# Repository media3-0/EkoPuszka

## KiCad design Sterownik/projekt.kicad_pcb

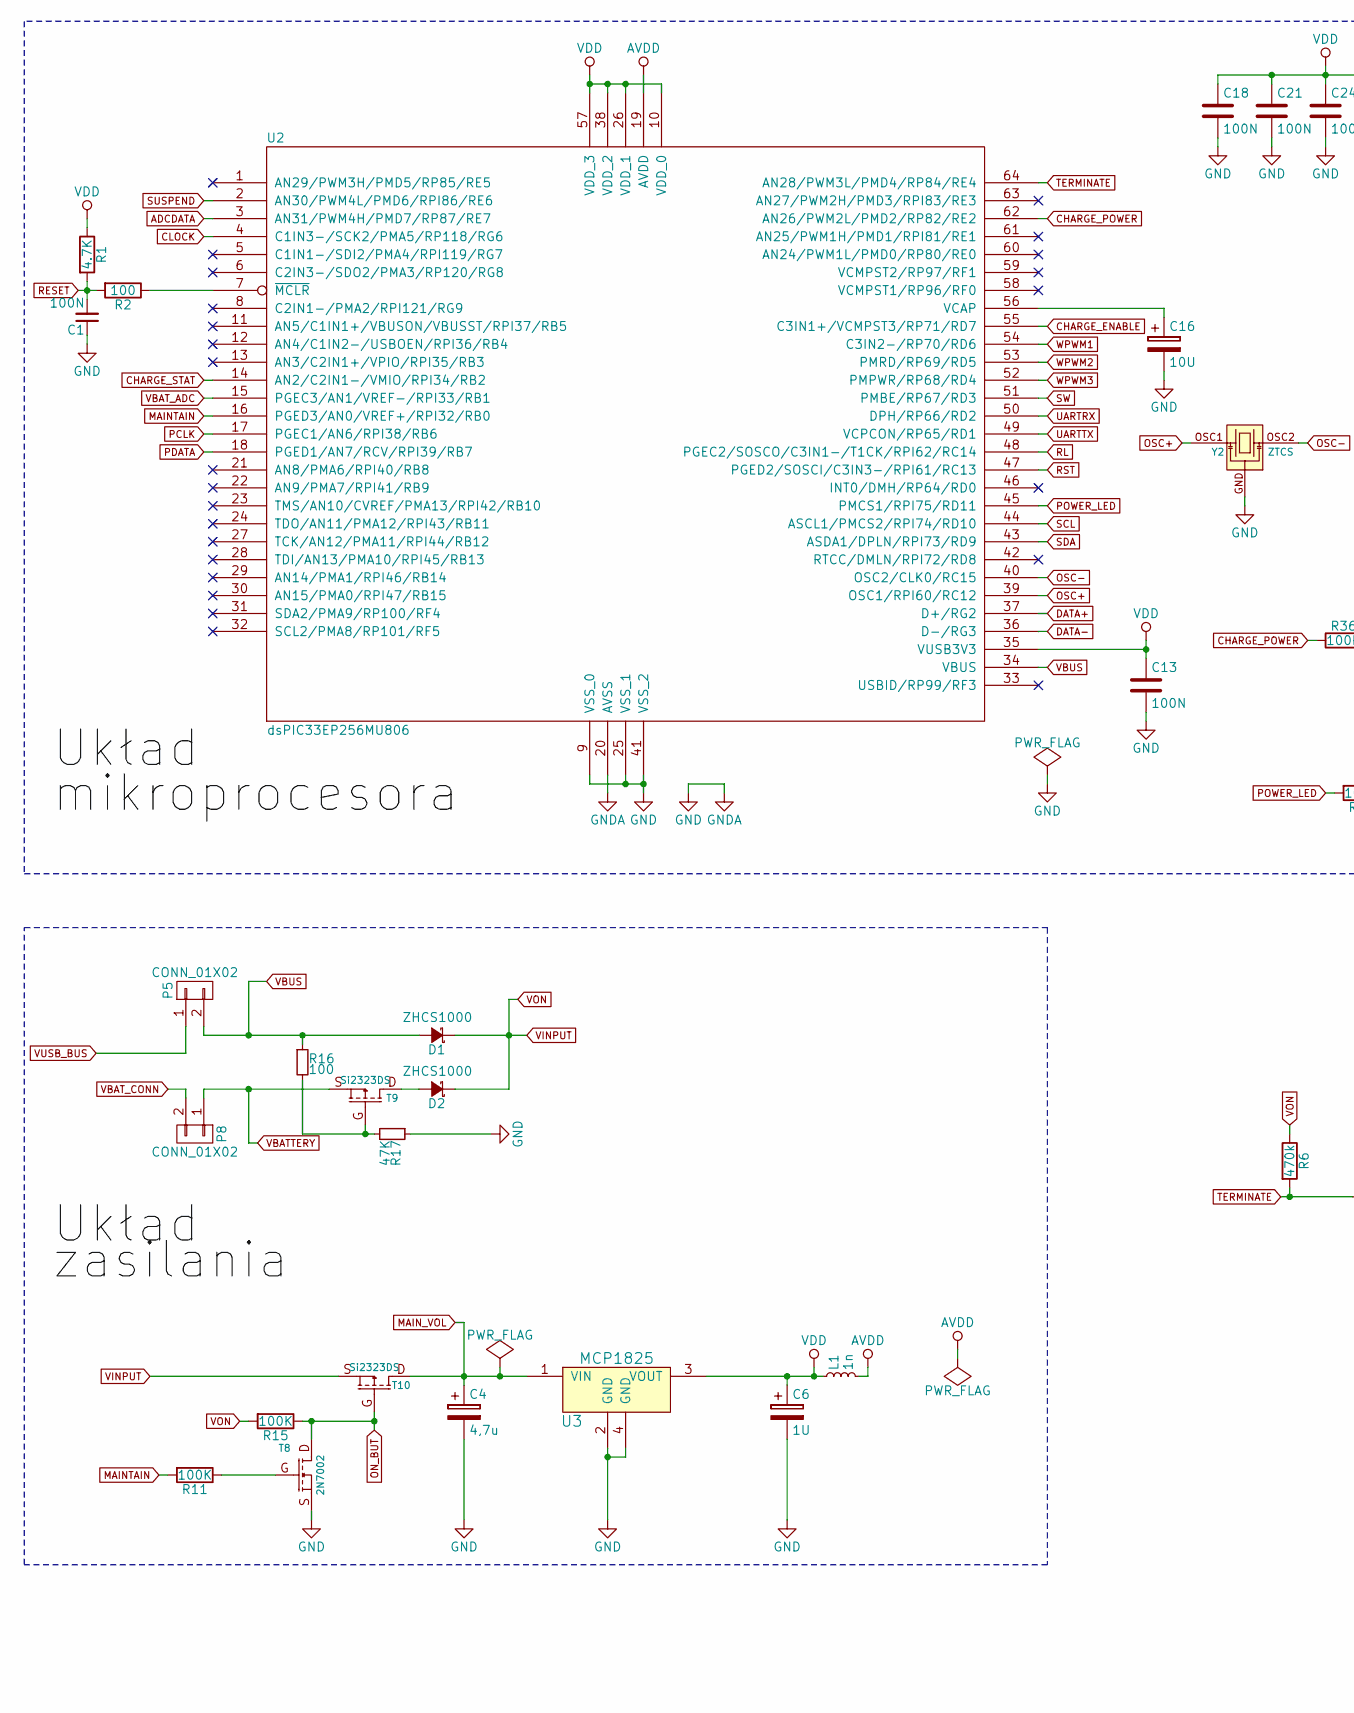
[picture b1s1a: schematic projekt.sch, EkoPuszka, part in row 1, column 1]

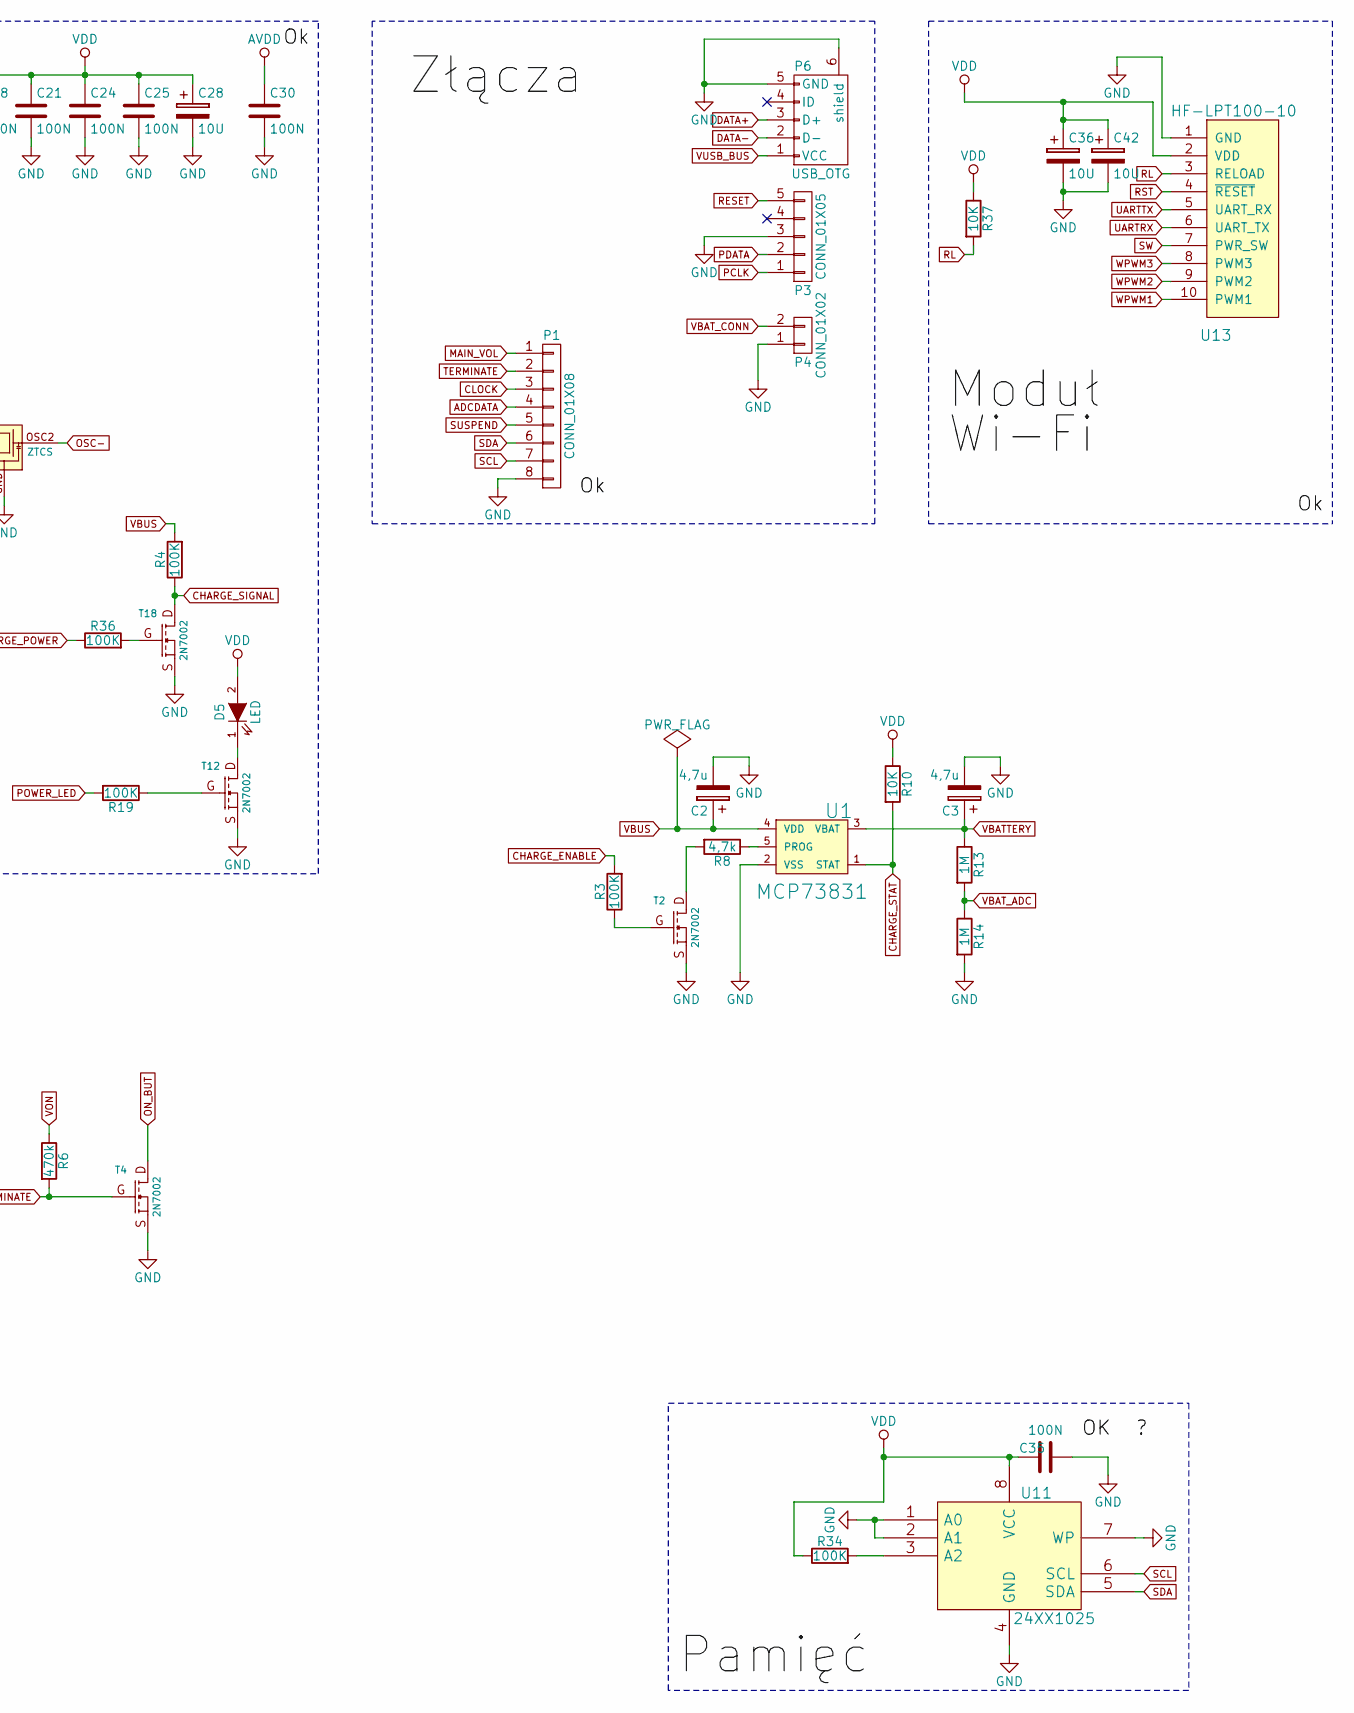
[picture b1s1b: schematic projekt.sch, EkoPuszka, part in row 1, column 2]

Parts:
C1, C13, C18, C21, C24, C25, C30, C35: 100N; C_0603_HandSoldering
C2, C3, C4: 4,7u; TantalC_SizeA_EIA-3216_HandSoldering
C6: 1U; C_2220_HandSoldering
C16: 10U; TantalC_SizeX_EIA-7343
C28, C36, C42: 10U; SMD-1206_Pol
D1, D2: ZHCS1000; SOT23-ZHCS1000
D5: LED; LED-1206
L1: 1n; R_0603
P1: CONN_01X08; DS1065-02-1X8S8BS
P3: CONN_01X05; Socket_Strip_Straight_1x05
P4: CONN_01X02; Socket_Strip_Straight_1x02
P5, P8: CONN_01X02; Pin_Header_Straight_1x02
P6: USB_OTG; USB_Mini-B
R1: 4.7K; R_0603
R2, R16: 100; R_0603
R3, R4, R11, R15, R19, R34, R36: 100K; R_0603
R6: 470k; R_0603
R8: 4,7k; R_0603
R10, R37: 10K; R_0603
R13, R14: 1M; R_0603
R17: 47K; R_0603
T2, T4, T8, T12, T18: 2N7002; 2N7002-SOT23
T9, T10: Si2323DS; SOT23
U1: MCP73831; SOT-23-5
U2: dsPIC33EP256MU806; TQFP-64_10x10mm_Pitch0.5mm
U3: MCP1825; SOT-223
U11: 24XX1025; SOIC-8-N
U13: HF-LPT100-10
Y2: ZTCS; ZTTCS

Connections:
ADCDATA: P1.4, U2.3 (AN31/PWM4H/PMD7/RP87/RE7)
AVDD: C30.1, L1.2, U2.19 (AVDD)
CHARGE_ENABLE: R3.2, U2.55 (C3IN1+/VCMPST3/RP71/RD7)
CHARGE_POWER: R36.1, U2.62 (AN26/PWM2L/PMD2/RP82/RE2)
CHARGE_SIGNAL: R4.1, T18.D
CHARGE_STAT: R10.2, U1.1 (STAT), U2.14 (AN2/C2IN1-/VMIO/RPI34/RB2)
CLOCK: P1.3, U2.4 (C1IN3-/SCK2/PMA5/RP118/RG6)
DATA+: P6.3 (D+), U2.37 (D+/RG2)
DATA-: P6.2 (D-), U2.36 (D-/RG3)
GND: C1.1, C2.2, C3.2, C4.2, C6.2, C13.2, C16.2, C18.2, C21.2, C24.2, C25.2, C28.2, C30.2, C35.1, C36.2, C42.2, P1.8, P3.3, P4.1, P6.5 (GND), P6.6 (shield), R14.2, R17.1, T2.S, T4.S, T8.S, T12.S, T18.S, U1.2 (VSS), U2.9 (VSS_0), U2.20 (AVSS), U2.25 (VSS_1), U2.41 (VSS_2), U3.2 (GND), U3.4 (GND), U11.1 (A0), U11.2 (A1), U11.4 (GND), U11.7 (WP), U13.1 (GND), Y2.GND
MAINTAIN: R11.2, U2.16 (PGED3/AN0/VREF+/RPI32/RB0)
MAIN_VOL: C4.1, P1.1, T10.D, U3.1 (VIN)
unnamed: C16.1, U2.56 (VCAP)
unnamed: D2.A, T9.D
unnamed: D5.1 (K), T12.D
unnamed: R2.1, U2.7 (~MCLR~)
unnamed: R3.1, T2.G
unnamed: R8.1, U1.5 (PROG)
unnamed: R8.2, T2.D
unnamed: R11.1, T8.G
unnamed: R16.2, R17.2, T9.G
unnamed: R19.1, T12.G
unnamed: R34.2, U11.3 (A2)
unnamed: R36.2, T18.G
ON_BUT: R15.1, T4.D, T8.D, T10.G
OSC+: U2.39 (OSC1/RPI60/RC12), Y2.OSC1
OSC-: U2.40 (OSC2/CLK0/RC15), Y2.OSC2
PCLK: P3.1, U2.17 (PGEC1/AN6/RPI38/RB6)
PDATA: P3.2, U2.18 (PGED1/AN7/RCV/RPI39/RB7)
POWER_LED: R19.2, U2.45 (PMCS1/RPI75/RD11)
RESET: C1.2, P3.5, R1.2, R2.2
RL: R37.2, U2.48 (PGEC2/SOSCO/C3IN1-/T1CK/RPI62/RC14), U13.3 (RELOAD)
RST: U2.47 (PGED2/SOSCI/C3IN3-/RPI61/RC13), U13.4 (~RESET)
SCL: P1.7, U2.44 (ASCL1/PMCS2/RPI74/RD10), U11.6 (SCL)
SDA: P1.6, U2.43 (ASDA1/DPLN/RPI73/RD9), U11.5 (SDA)
SUSPEND: P1.5, U2.2 (AN30/PWM4L/PMD6/RPI86/RE6)
SW: U2.51 (PMBE/RP67/RD3), U13.7 (PWR_SW)
TERMINATE: P1.2, R6.2, T4.G, U2.64 (AN28/PWM3L/PMD4/RP84/RE4)
UARTRX: U2.50 (DPH/RP66/RD2), U13.6 (UART_TX)
UARTTX: U2.49 (VCPCON/RP65/RD1), U13.5 (UART_RX)
VBATTERY: C3.1, P8.1, R13.1, T9.S, U1.3 (VBAT)
VBAT_ADC: R13.2, R14.1, U2.15 (PGEC3/AN1/VREF-/RPI33/RB1)
VBAT_CONN: P4.2, P8.2
VBUS: C2.1, D1.A, P5.2, R4.2, R16.1, U1.4 (VDD), U2.34 (VBUS)
VDD: C6.1, C13.1, C18.1, C21.1, C24.1, C25.1, C28.1, C35.2, C36.1, C42.1, D5.2 (A), L1.1, R1.1, R10.1, R34.1, R37.1, U2.10 (VDD_0), U2.26 (VDD_1), U2.35 (VUSB3V3), U2.38 (VDD_2), U2.57 (VDD_3), U3.3 (VOUT), U11.8 (VCC), U13.2 (VDD)
VINPUT: D1.C, D2.C, R6.1, R15.2, T10.S
VUSB_BUS: P5.1, P6.1 (VCC)
WPWM1: U2.54 (C3IN2-/RP70/RD6), U13.10 (PWM1)
WPWM2: U2.53 (PMRD/RP69/RD5), U13.9 (PWM2)
WPWM3: U2.52 (PMPWR/RP68/RD4), U13.8 (PWM3)

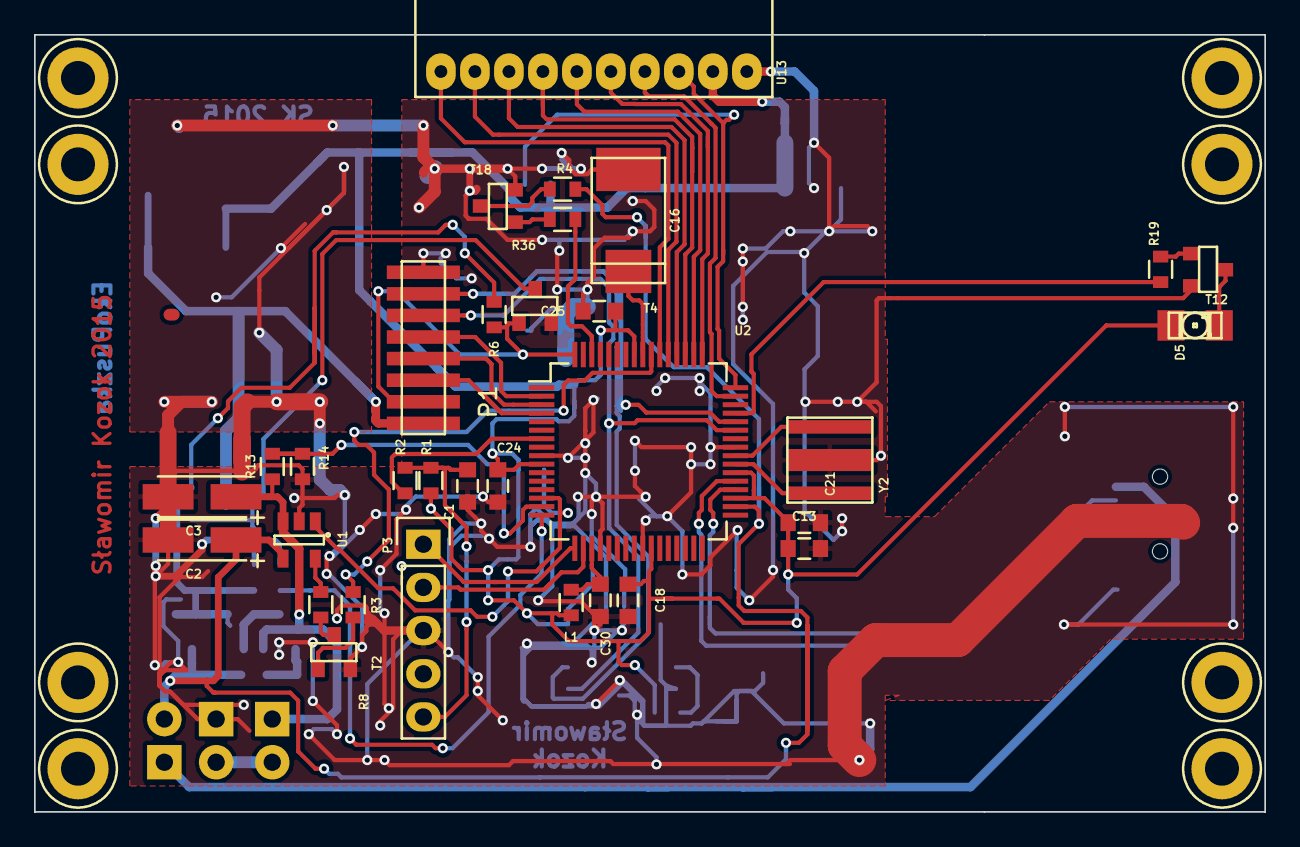
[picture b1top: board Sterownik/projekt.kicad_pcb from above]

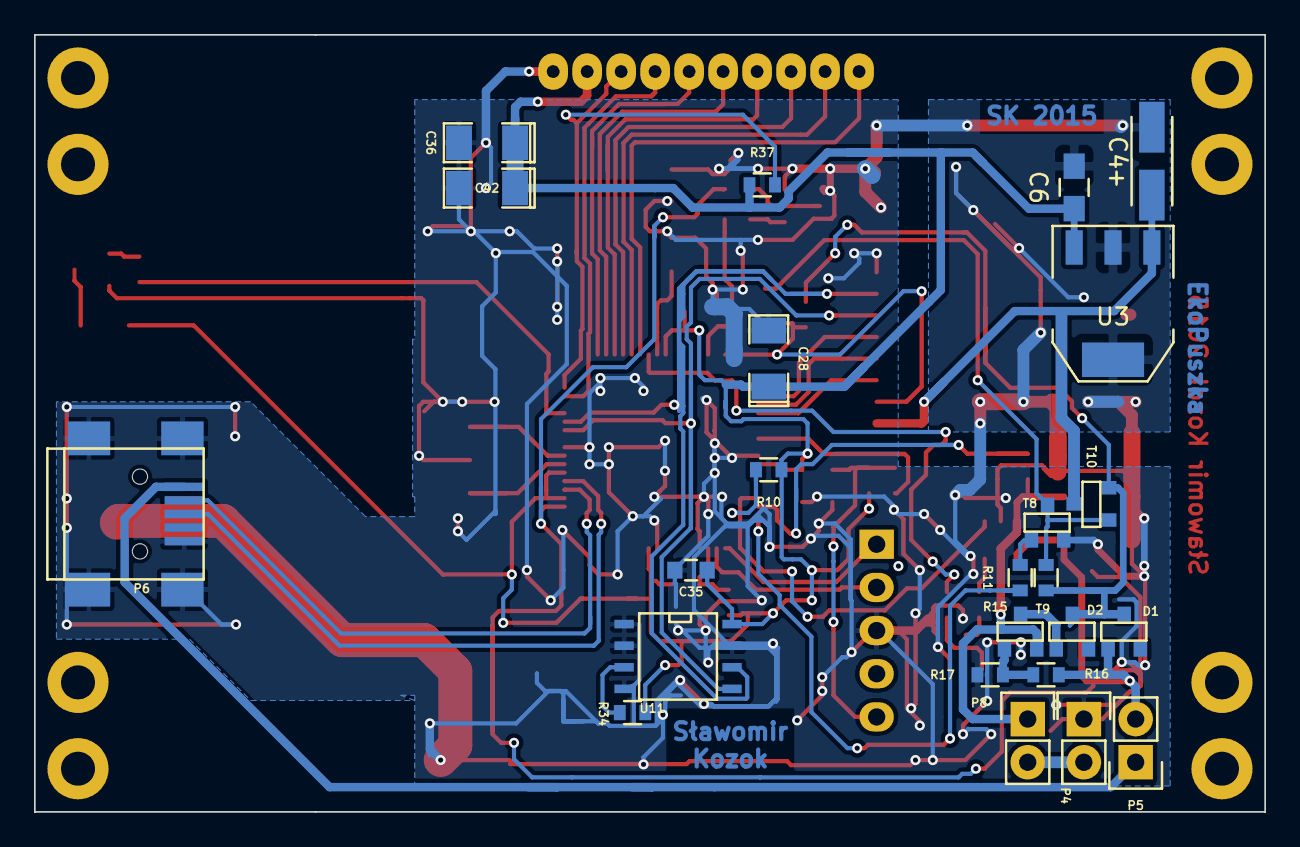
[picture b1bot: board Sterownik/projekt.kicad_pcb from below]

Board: 2 copper layers, 72.4 x 45.7 mm, 56 parts (24 on the bottom side), 50 nets.

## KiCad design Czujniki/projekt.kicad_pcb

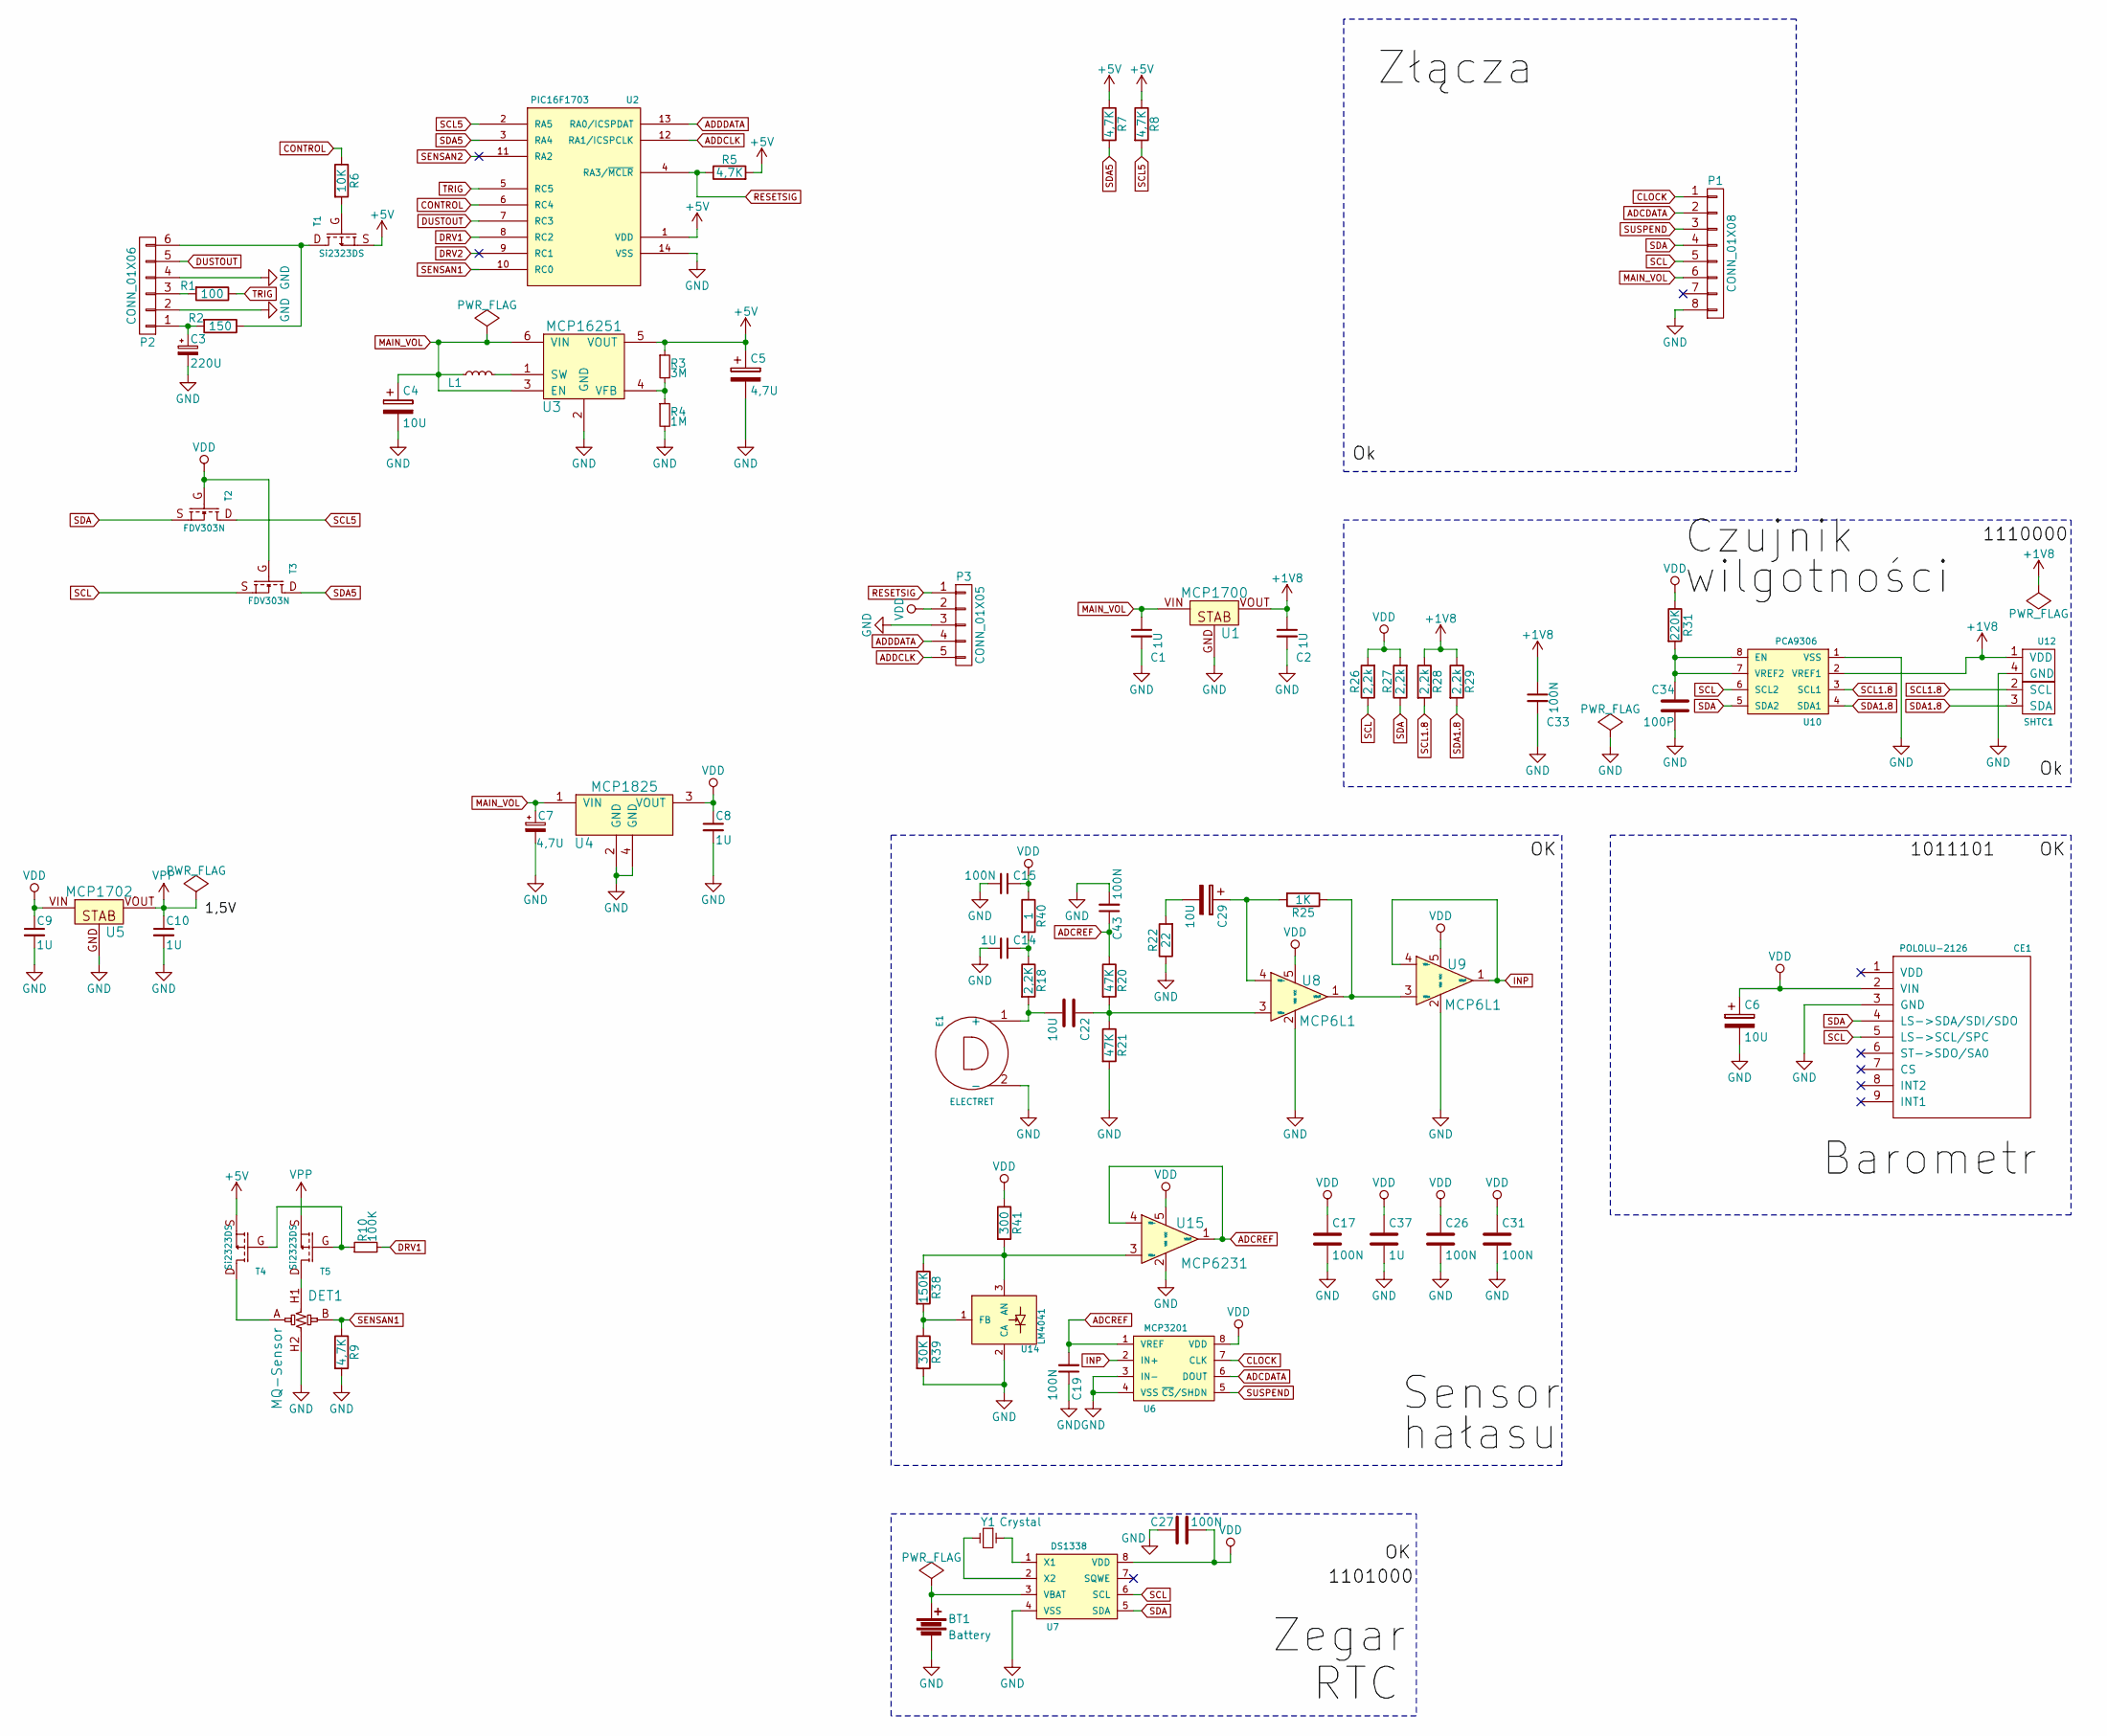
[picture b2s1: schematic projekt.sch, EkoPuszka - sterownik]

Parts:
BT1: Battery; CR2032H
C1, C2, C8, C9, C10, C14, C37: 1U; C_0805_HandSoldering
C3: 220U; TantalC_SizeX_EIA-7343
C4: 10U; TantalC_SizeX_EIA-7343
C5, C7: 4,7U; TantalC_SizeA_EIA-3216_HandSoldering
C6, C22, C29: 10U; SMD-1206_Pol
C15, C17, C19, C26, C27, C31, C33, C43: 100N; C_0603_HandSoldering
C34: 100P; C_0603_HandSoldering
CE1: POLOLU-2126; Socket_Strip_Straight_1x09
DET1: MQ-Sensor; Socket_Strip_Straight_1x06
E1: ELECTRET; Pin_Header_Straight_1x02
L1: NLCV32T-4R7M-PF; SMD-1210_Pol
P1: CONN_01X08; DS1065-02-1X8S8BS
P2: CONN_01X06; Socket_Strip_Straight_1x06
P3: CONN_01X05; Socket_Strip_Straight_1x05
R1: 100; R_0603
R2: 150; R_0805
R3: 3M; R_0603
R4: 1M; R_0603
R5, R7, R8, R9: 4,7K; R_0603
R6: 10K; R_0603
R10: 100K; R_0603
R18: 2,2K; R_0603
R20, R21: 47K; R_0603
R22: 22; R_0603
R25: 1K; R_0603
R26, R27, R28, R29: 2,2k; R_0603
R31: 220K; R_0603
R38: 150K; R_0603
R39: 30K; R_0603
R40: 1; R_0603
R41: 300; R_0603
T1, T4, T5: Si2323DS; SOT23
T2, T3: FDV303N; SOT23
U1: MCP1700; SOT23-mcp1700
U2: PIC16F1703; SOIC-14_N
U3: MCP16251; SOT-23-6
U4: MCP1825; SOT-223
U5: MCP1702; SOT23-mcp1700
U6: MCP3201; SOIC-8-N
U7: DS1338; SOIC-8-N
U8, U9: MCP6L1; SOT-23-5
U10: PCA9306; TSSOP-8_3x3mm_Pitch0.65mm
U12: SHTC1; DFN4-2x2x0.75
U14: LM4041; SOT-23_Handsoldering
U15: MCP6231; SOT-23-5
Y1: Crystal; 91SMX-OSC

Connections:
+1V8: C2.1, C33.1, R28.1, R29.1, U1.VOUT, U10.2 (VREF1), U12.1 (VDD)
+5V: C5.1, R3.1, R5.2, R7.1, R8.1, T1.S, T4.S, U2.1 (VDD), U3.5 (VOUT)
ADCDATA: P1.2, U6.6 (DOUT)
ADCREF: C19.2, C43.1, R20.1, U6.1 (VREF), U15.1 (VOUT), U15.4 (VIN-)
ADDCLK: P3.5, U2.12 (RA1/ICSPCLK)
ADDDATA: P3.4, U2.13 (RA0/ICSPDAT)
CLOCK: P1.1, U6.7 (CLK)
CONTROL: R6.1, U2.6 (RC4)
DRV1: R10.2, U2.8 (RC2)
DUSTOUT: P2.5, U2.7 (RC3)
GND: BT1.2, C1.2, C2.2, C3.2, C4.2, C5.2, C6.2, C7.2, C8.2, C9.2, C10.2, C14.2, C15.2, C17.2, C19.1, C26.2, C27.2, C31.2, C33.2, C34.2, C37.2, C43.2, CE1.3 (GND), DET1.H2, E1.2 (-), P1.8, P2.2, P2.4, P3.3, R4.2, R9.2, R21.2, R22.1, R39.2, U1.GND, U2.14 (VSS), U3.2 (GND), U4.2 (GND), U4.4 (GND), U5.GND, U6.3 (IN-), U6.4 (VSS), U7.4 (VSS), U8.2 (VSS), U9.2 (VSS), U10.1 (VSS), U12.4 (GND), U14.2 (CA), U15.2 (VSS)
INP: U6.2 (IN+), U9.1 (VOUT), U9.4 (VIN-)
MAIN_VOL: C1.1, C4.1, C7.1, L1.1, P1.6, U1.VIN, U3.3 (EN), U3.6 (VIN), U4.1 (VIN)
unnamed: BT1.1, U7.3 (VBAT)
unnamed: C3.1, P2.1, R2.2
unnamed: C14.1, R18.1, R40.2
unnamed: C22.1, R20.2, R21.1, U8.3 (VIN+)
unnamed: C22.2, E1.1 (+), R18.2
unnamed: C29.1, R25.2, U8.4 (VIN-)
unnamed: C29.2, R22.2
unnamed: C34.1, R31.2, U10.7 (VREF2), U10.8 (EN)
unnamed: DET1.A, T4.D
unnamed: DET1.H1, T5.D
unnamed: L1.2, U3.1 (SW)
unnamed: P2.3, R1.2
unnamed: P2.6, R2.1, T1.D
unnamed: R3.2, R4.1, U3.4 (VFB)
unnamed: R6.2, T1.G
unnamed: R10.1, T4.G, T5.G
unnamed: R25.1, U8.1 (VOUT), U9.3 (VIN+)
unnamed: R38.1, R41.2, U14.3 (AN), U15.3 (VIN+)
unnamed: R38.2, R39.1, U14.1 (FB)
unnamed: U7.1 (X1), Y1.1
unnamed: U7.2 (X2), Y1.2
RESETSIG: P3.1, R5.1, U2.4 (RA3/~MCLR)
SCL: CE1.5 (LS->SCL/SPC), P1.5, R26.1, T3.S, U7.6 (SCL), U10.6 (SCL2)
SCL1.8: R28.2, U10.3 (SCL1), U12.2 (SCL)
SCL5: R8.2, T2.D, U2.2 (RA5)
SDA: CE1.4 (LS->SDA/SDI/SDO), P1.4, R27.1, T2.S, U7.5 (SDA), U10.5 (SDA2)
SDA1.8: R29.2, U10.4 (SDA1), U12.3 (SDA)
SDA5: R7.2, T3.D, U2.3 (RA4)
SENSAN1: DET1.B, R9.1, U2.10 (RC0)
SUSPEND: P1.3, U6.5 (~CS~/SHDN)
TRIG: R1.1, U2.5 (RC5)
VDD: C6.1, C8.1, C9.1, C15.1, C17.1, C26.1, C27.1, C31.1, C37.1, CE1.2 (VIN), P3.2, R26.2, R27.2, R31.1, R40.1, R41.1, T2.G, T3.G, U4.3 (VOUT), U5.VIN, U6.8 (VDD), U7.8 (VDD), U8.5 (VCC), U9.5 (VCC), U15.5 (VCC)
VPP: C10.1, T5.S, U5.VOUT

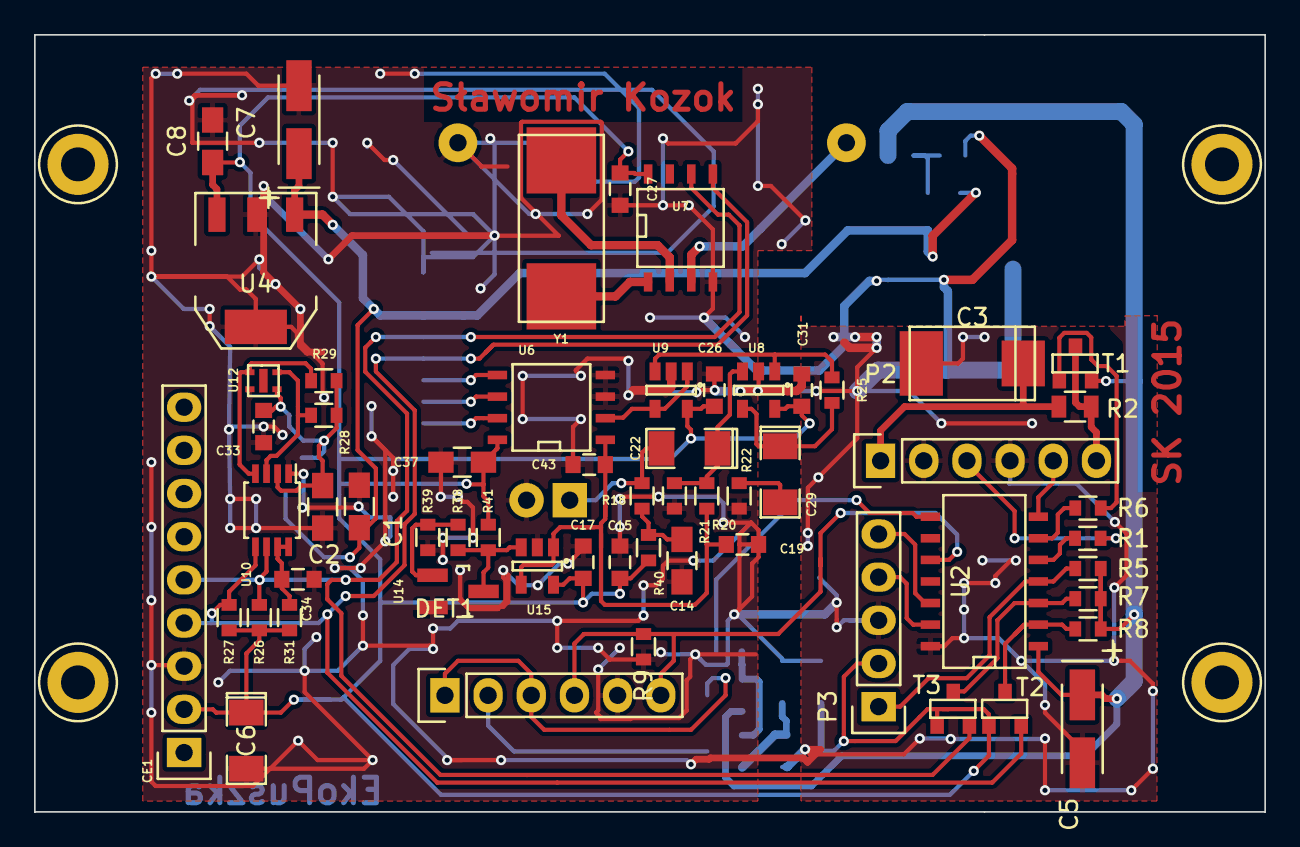
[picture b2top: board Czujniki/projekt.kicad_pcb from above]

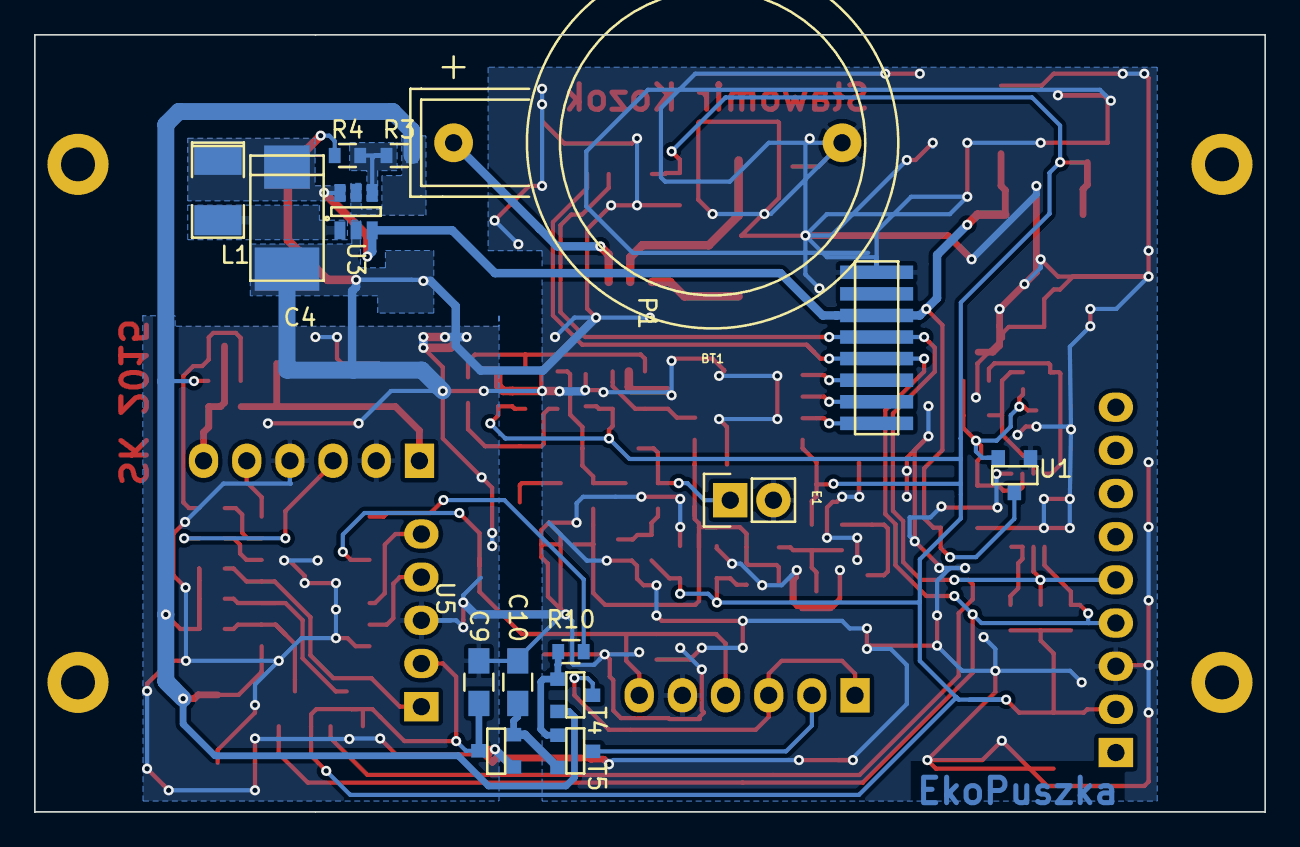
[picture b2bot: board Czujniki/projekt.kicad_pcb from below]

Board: 2 copper layers, 72.4 x 45.7 mm, 74 parts (15 on the bottom side), 46 nets.

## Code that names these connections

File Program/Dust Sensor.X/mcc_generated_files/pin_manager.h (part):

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// get/set SDA aliases
#define SDA_TRIS               TRISA4
#define SDA_LAT                LATA4
#define SDA_PORT               RA4
#define SDA_WPU                WPUA4
#define SDA_ANS                ANSA4
#define SDA_SetHigh()    do { LATA4 = 1; } while(0)
#define SDA_SetLow()   do { LATA4 = 0; } while(0)
#define SDA_Toggle()   do { LATA4 = ~LATA4; } while(0)
#define SDA_GetValue()         RA4
#define SDA_SetDigitalInput()    do { TRISA4 = 1; } while(0)
#define SDA_SetDigitalOutput()   do { TRISA4 = 0; } while(0)

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// get/set SCL aliases
#define SCL_TRIS               TRISA5
#define SCL_LAT                LATA5
#define SCL_PORT               RA5
#define SCL_WPU                WPUA5
#define SCL_SetHigh()    do { LATA5 = 1; } while(0)
#define SCL_SetLow()   do { LATA5 = 0; } while(0)
#define SCL_Toggle()   do { LATA5 = ~LATA5; } while(0)
#define SCL_GetValue()         RA5
#define SCL_SetDigitalInput()    do { TRISA5 = 1; } while(0)
#define SCL_SetDigitalOutput()   do { TRISA5 = 0; } while(0)

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// get/set channel_AN4 aliases
#define channel_AN4_TRIS               TRISC0
#define channel_AN4_LAT                LATC0
#define channel_AN4_PORT               RC0
#define channel_AN4_WPU                WPUC0
#define channel_AN4_ANS                ANSC0
#define channel_AN4_SetHigh()    do { LATC0 = 1; } while(0)
#define channel_AN4_SetLow()   do { LATC0 = 0; } while(0)
#define channel_AN4_Toggle()   do { LATC0 = ~LATC0; } while(0)
#define channel_AN4_GetValue()         RC0
#define channel_AN4_SetDigitalInput()    do { TRISC0 = 1; } while(0)
#define channel_AN4_SetDigitalOutput()   do { TRISC0 = 0; } while(0)

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// get/set IO_RC2 aliases
#define IO_RC2_TRIS               TRISC2
#define IO_RC2_LAT                LATC2
#define IO_RC2_PORT               RC2
#define IO_RC2_WPU                WPUC2
#define IO_RC2_ANS                ANSC2
#define IO_RC2_SetHigh()    do { LATC2 = 1; } while(0)
#define IO_RC2_SetLow()   do { LATC2 = 0; } while(0)
#define IO_RC2_Toggle()   do { LATC2 = ~LATC2; } while(0)
#define IO_RC2_GetValue()         RC2
#define IO_RC2_SetDigitalInput()    do { TRISC2 = 1; } while(0)
#define IO_RC2_SetDigitalOutput()   do { TRISC2 = 0; } while(0)

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// get/set channel_AN7 aliases
#define channel_AN7_TRIS               TRISC3
#define channel_AN7_LAT                LATC3
#define channel_AN7_PORT               RC3
#define channel_AN7_WPU                WPUC3
#define channel_AN7_ANS                ANSC3
#define channel_AN7_SetHigh()    do { LATC3 = 1; } while(0)
#define channel_AN7_SetLow()   do { LATC3 = 0; } while(0)
#define channel_AN7_Toggle()   do { LATC3 = ~LATC3; } while(0)
#define channel_AN7_GetValue()         RC3
#define channel_AN7_SetDigitalInput()    do { TRISC3 = 1; } while(0)
#define channel_AN7_SetDigitalOutput()   do { TRISC3 = 0; } while(0)

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// get/set IO_RC4 aliases
#define IO_RC4_TRIS               TRISC4
#define IO_RC4_LAT                LATC4
#define IO_RC4_PORT               RC4
#define IO_RC4_WPU                WPUC4
#define IO_RC4_ANS                ANSC4
#define IO_RC4_SetHigh()    do { LATC4 = 1; } while(0)
#define IO_RC4_SetLow()   do { LATC4 = 0; } while(0)
#define IO_RC4_Toggle()   do { LATC4 = ~LATC4; } while(0)
#define IO_RC4_GetValue()         RC4
#define IO_RC4_SetDigitalInput()    do { TRISC4 = 1; } while(0)
#define IO_RC4_SetDigitalOutput()   do { TRISC4 = 0; } while(0)

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// get/set IO_RC5 aliases
#define IO_RC5_TRIS               TRISC5
#define IO_RC5_LAT                LATC5
#define IO_RC5_PORT               RC5
#define IO_RC5_WPU                WPUC5
#define IO_RC5_ANS                ANSC5
#define IO_RC5_SetHigh()    do { LATC5 = 1; } while(0)
#define IO_RC5_SetLow()   do { LATC5 = 0; } while(0)
#define IO_RC5_Toggle()   do { LATC5 = ~LATC5; } while(0)
#define IO_RC5_GetValue()         RC5
#define IO_RC5_SetDigitalInput()    do { TRISC5 = 1; } while(0)
#define IO_RC5_SetDigitalOutput()   do { TRISC5 = 0; } while(0)

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
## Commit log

2015-07-16 First commit in new repo
    All files
2015-07-16 Additional changes
2015-07-17 100% driver PCB routed - waiting for fixes
2015-07-20 Fixes commit.
2015-07-20 Deleting additional files.
2015-07-20 More fixes
2015-07-21 Working on sensor board
2015-07-21 Simplifiying all
2015-07-21 Simplier version - first fixes
2015-07-21 More fixes and new trace placing
2015-07-22 DC/DC converter to linear converter change
2015-07-22 Edits + additional program for dust controller
2015-07-23 Commit message
2015-07-23 Some adds. Dust sensor program little addition.
2015-07-23 Commit Repair
2015-07-23 Fixes after bad commit. Making bigger board.
2015-07-23 Supply on sensor board done. Before gas sensor adding.
2015-07-24 Sensor added in board.
2015-07-24 All things on PCB.
2015-07-27 GND on sensor board for routing.
2015-07-27 Ground plane and license.
2015-07-27 Cleaning repo
2015-07-27 License, PCB update.
2015-07-28 Adding license files. PCB ready for fixes.
2015-07-28 Changed gitignore.
2015-07-28 Change board sizes.
2015-07-29 Changed switch placement (from main to sensor board)

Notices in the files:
Program/Dust Sensor.X/mcc_generated_files/pin_manager.h:
Copyright (c) 2013 - 2015 released Microchip Technology Inc.  All rights reserved.
The MIT License (MIT)
Copyright (c) 2015 S?awomir Kozok
